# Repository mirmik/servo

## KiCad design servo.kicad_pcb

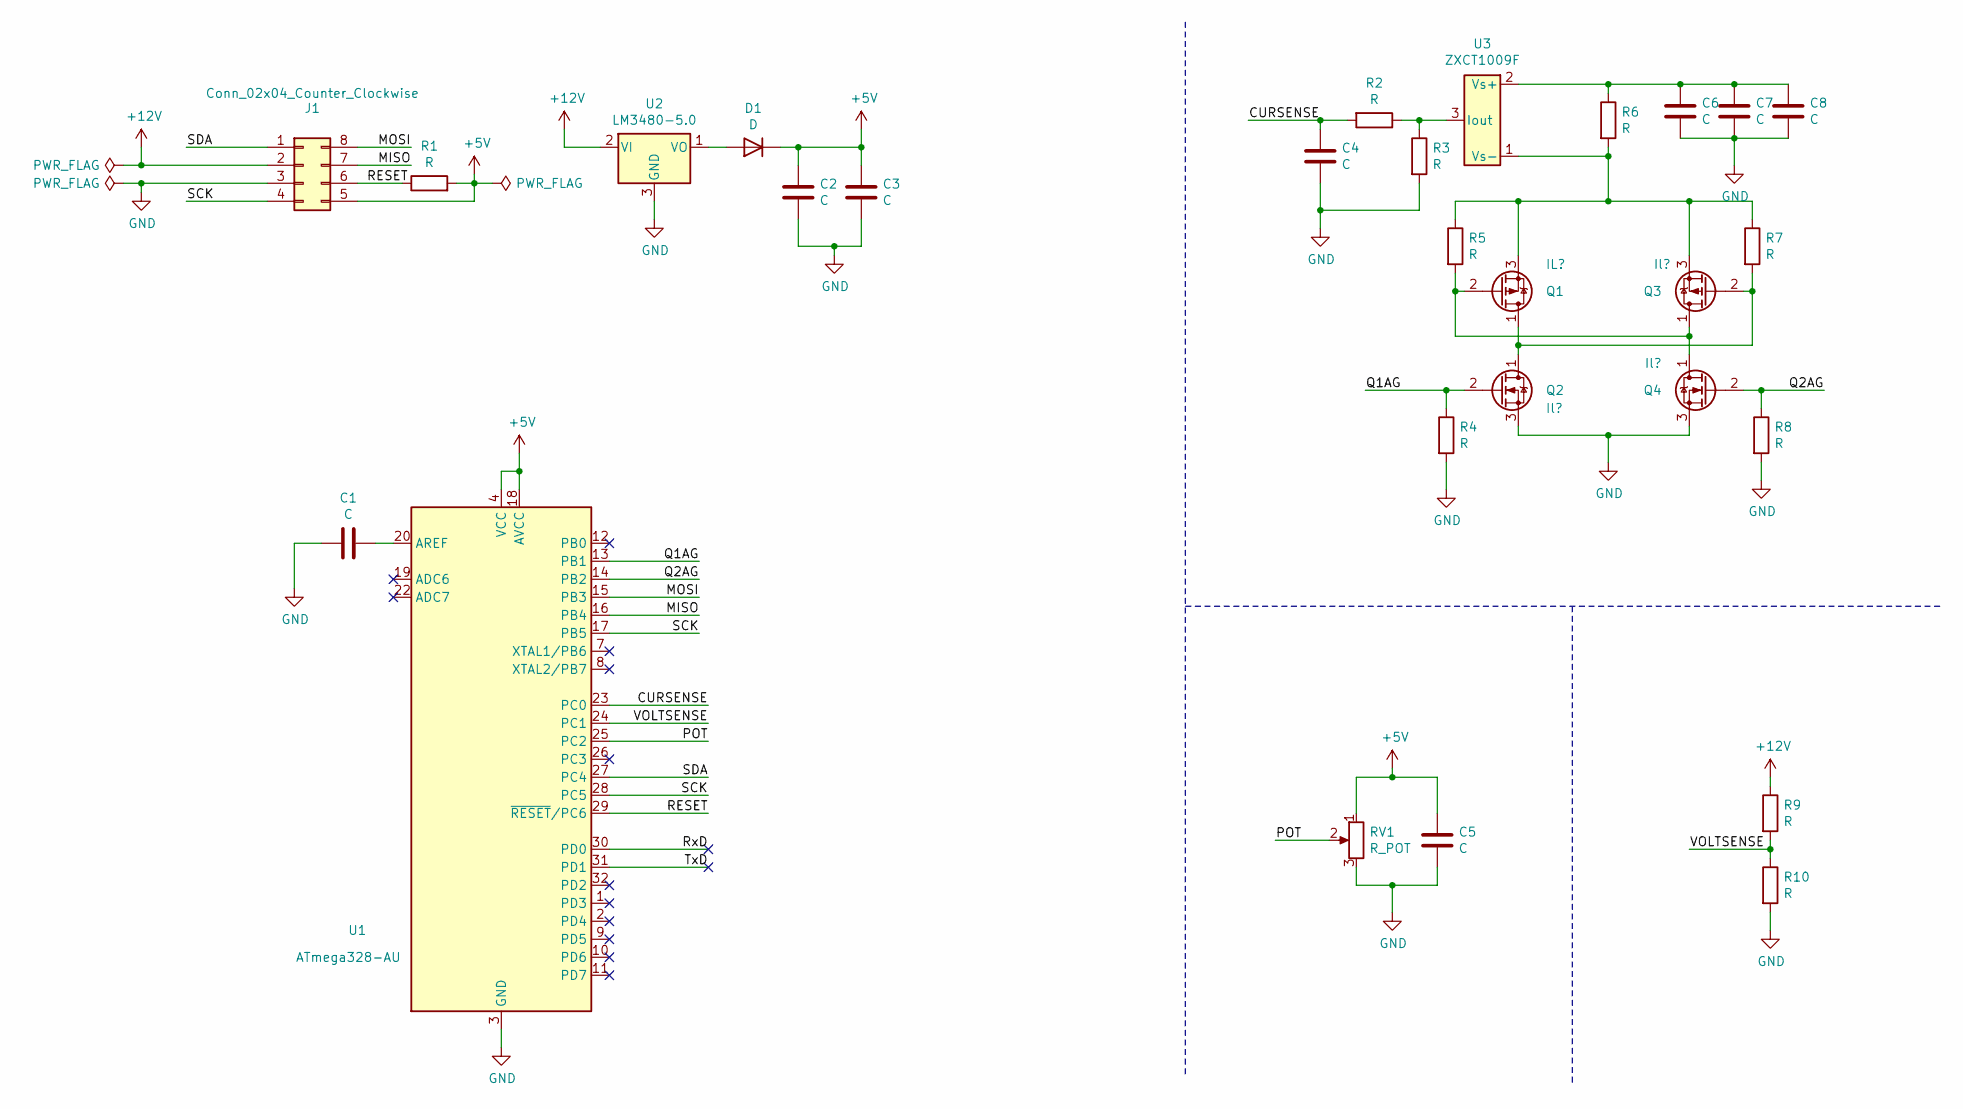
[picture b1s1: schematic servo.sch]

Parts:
C1, C2, C3, C4, C5, C6, C7, C8: C; C_0805_2012Metric
D1: D; D_3220_8050Metric
J1: Conn_02x04_Counter_Clockwise; PinHeader_2x04_P2.00mm_Horizontal
Q1: IL?; SOT-223-3_TabPin2
Q2, Q3, Q4: Il?; SOT-223-3_TabPin2
R1, R2, R3, R4, R5, R6, R7, R8, R9, R10: R; R_0805_2012Metric
RV1: R_POT; PinHeader_1x03_P2.54mm_Horizontal
U1: ATmega328-AU; TQFP-32_7x7mm_P0.8mm
U2: LM3480-5.0; SOT-23
U3: ZXCT1009F; SOT-23

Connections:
+5V: C2.1, C3.1, C5.1, D1.1 (K), J1.5, R1.2, RV1.1, U1.4 (VCC), U1.6 (VCC), U1.18 (AVCC)
+12V: J1.2, R9.1, U2.2 (VI)
/CURSENSE: C4.1, R2.2, U1.23 (PC0)
/MISO: J1.7, U1.16 (PB4)
/MOSI: J1.8, U1.15 (PB3)
/POT: RV1.2, U1.25 (PC2)
/Q1AG: Q2.2 (G), R4.1, U1.13 (PB1)
/Q2AG: Q4.2 (G), R8.1, U1.14 (PB2)
/RESET: J1.6, R1.1, U1.29 (~RESET~/PC6)
/RxD: U1.30 (PD0)
/SCK: J1.4, U1.17 (PB5), U1.28 (PC5)
/SDA: J1.1, U1.27 (PC4)
/TxD: U1.31 (PD1)
/VOLTSENSE: R9.2, R10.1, U1.24 (PC1)
GND: C1.1, C2.2, C3.2, C4.2, C5.2, C6.2, C7.2, C8.2, J1.3, Q2.3 (S), Q4.3 (S), R3.2, R4.2, R8.2, R10.2, RV1.3, U1.3 (GND), U1.5 (GND), U1.21 (GND), U2.3 (GND)
unnamed: C1.2, U1.20 (AREF)
unnamed: C6.1, C7.1, C8.1, R6.1, U3.2 (Vs+)
unnamed: D1.2 (A), U2.1 (VO)
unnamed: Q1.1 (D), Q2.1 (D), Q3.2 (G), R7.2
unnamed: Q1.2 (G), Q3.1 (D), Q4.1 (D), R5.2
unnamed: Q1.3 (S), Q3.3 (S), R5.1, R6.2, R7.1, U3.1 (Vs-)
unnamed: R2.1, R3.1, U3.3 (Iout)

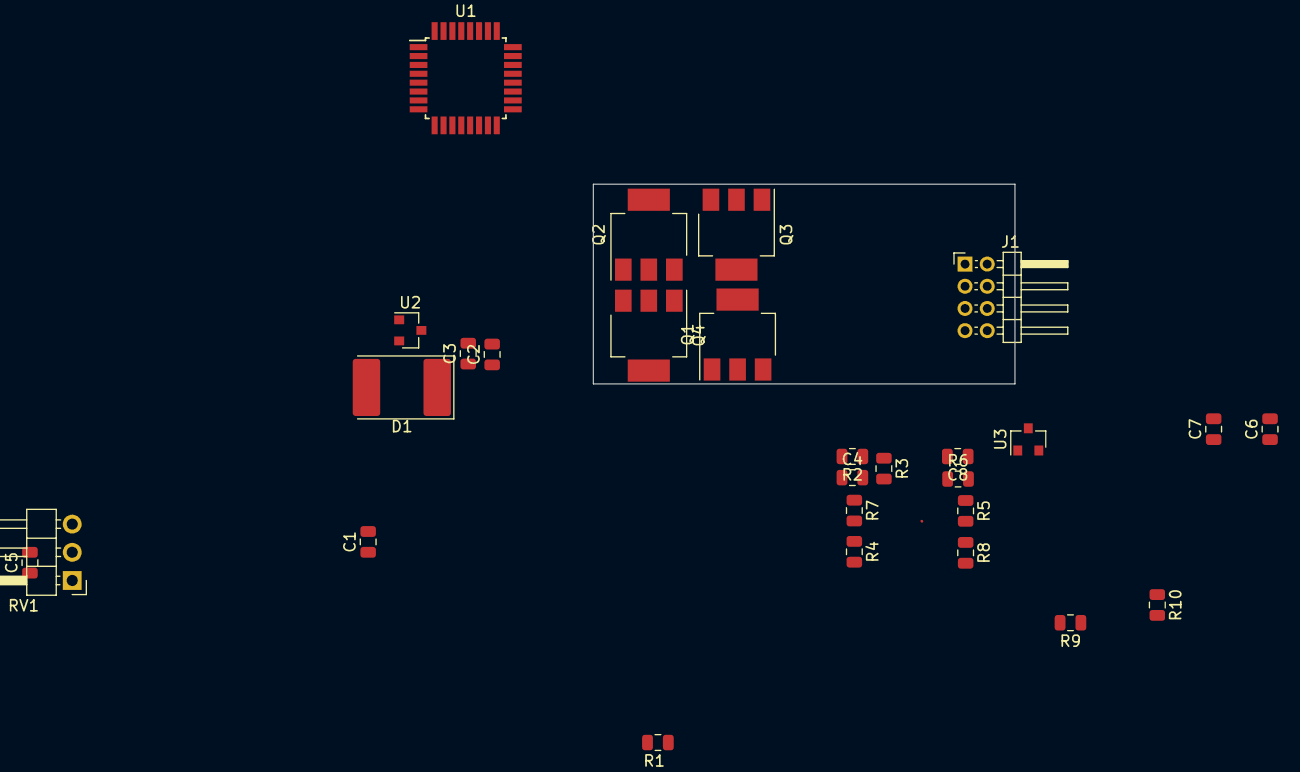
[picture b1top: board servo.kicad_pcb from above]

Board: 2 copper layers, 38.0 x 18.0 mm, 28 parts (0 on the bottom side), 20 nets.
